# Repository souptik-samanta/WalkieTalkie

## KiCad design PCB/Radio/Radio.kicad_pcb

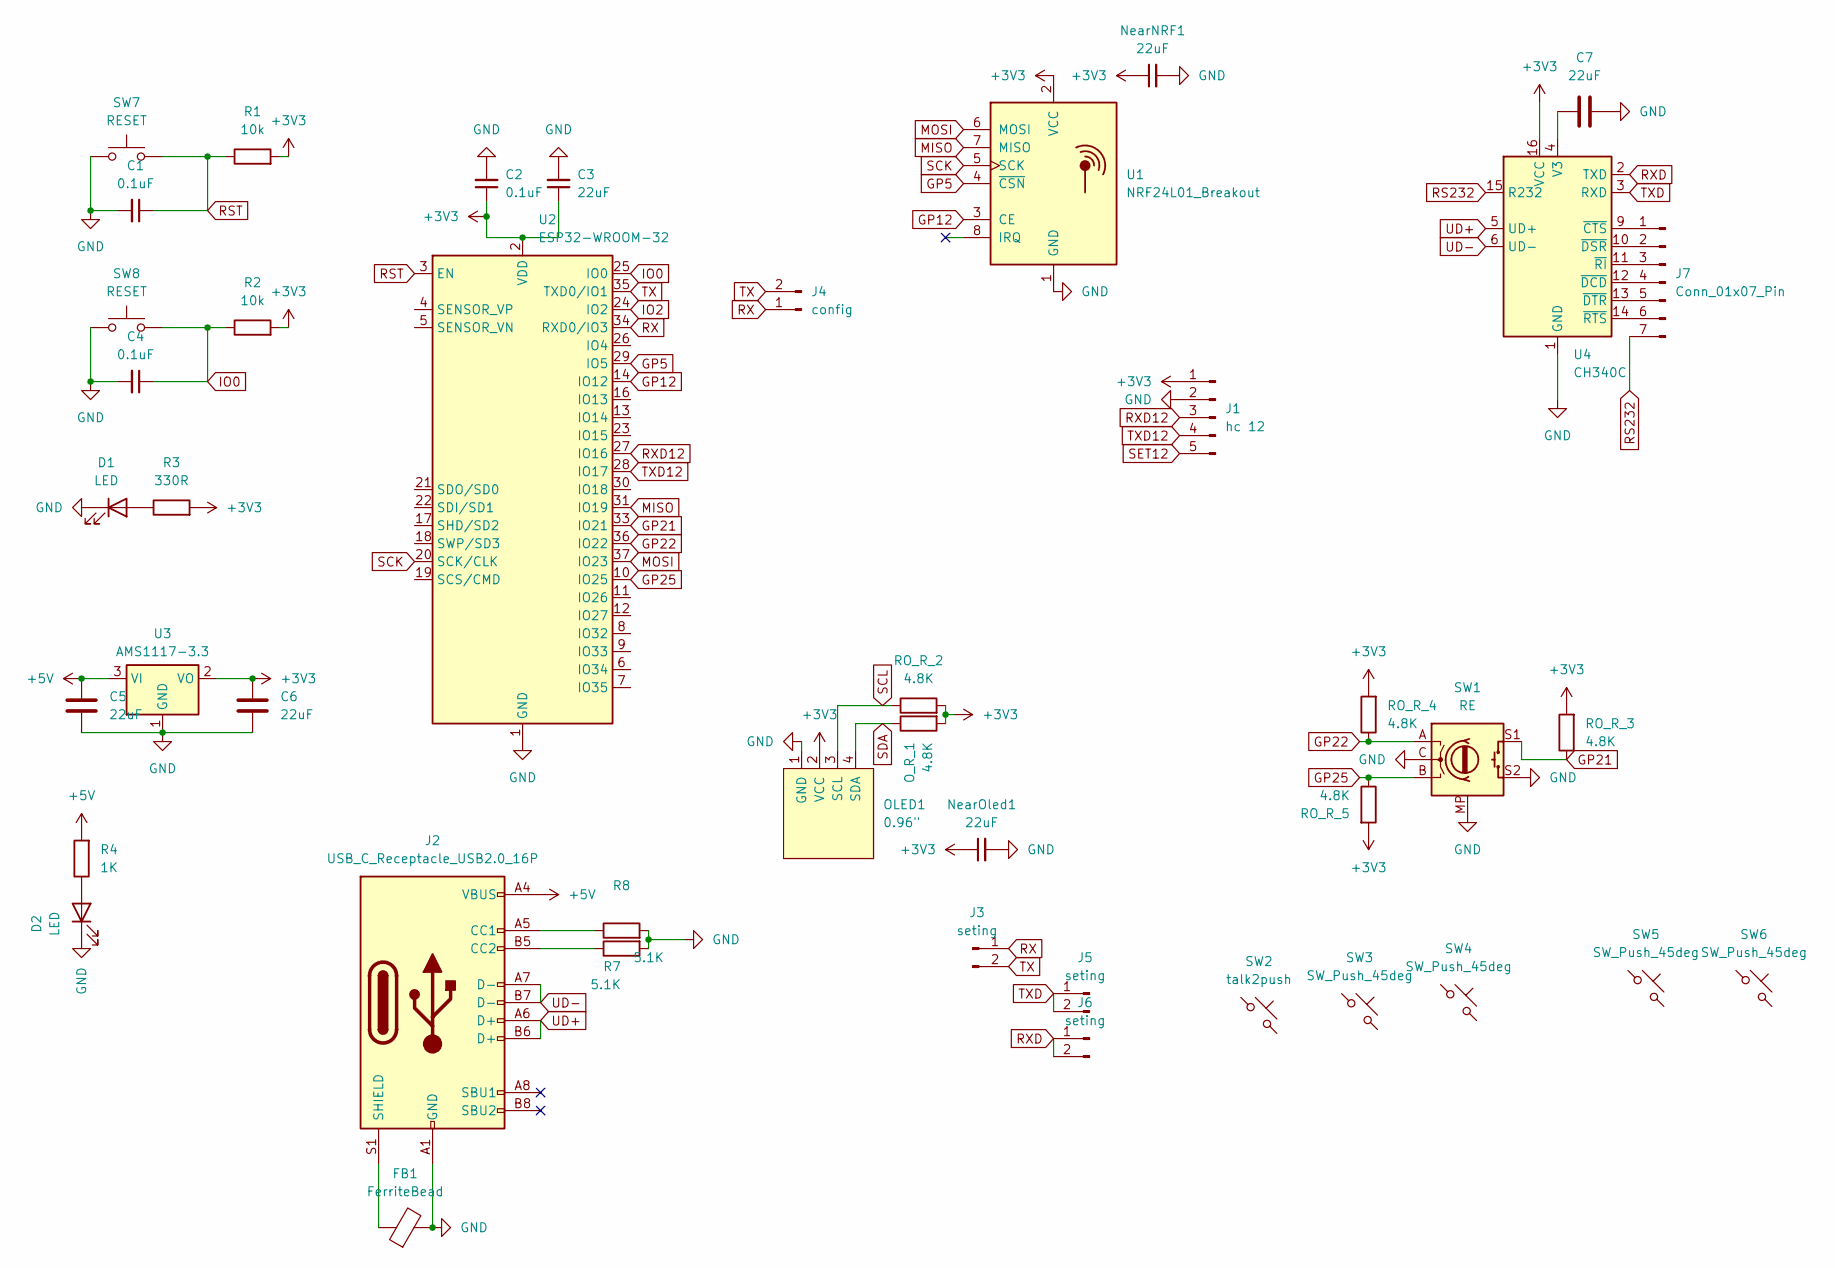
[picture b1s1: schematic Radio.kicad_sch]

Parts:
C1, C2, C4: 0.1uF; C_1206_3216Metric_Pad1.33x1.80mm_HandSolder
C3, C5, C6, C7: 22uF; C_1206_3216Metric_Pad1.33x1.80mm_HandSolder
D1, D2: LED; LED_1206_3216Metric_Pad1.42x1.75mm_HandSolder
FB1: FerriteBead; L_1206_3216Metric_Pad1.42x1.75mm_HandSolder
J1: hc 12; Hirose_DF13-05P-1.25DSA_1x05_P1.25mm_Vertical
J2: USB_C_Receptacle_USB2.0_16P; USB_C_Receptacle_HRO_TYPE-C-31-M-12
J3, J5, J6: seting; PinHeader_1x02_P2.54mm_Vertical
J4: config; PinHeader_1x02_P2.54mm_Vertical
J7: Conn_01x07_Pin; PinHeader_1x07_P2.54mm_Vertical
NearNRF1: 22uF; C_1206_3216Metric_Pad1.33x1.80mm_HandSolder
NearOled1: 22uF; C_1206_3216Metric_Pad1.33x1.80mm_HandSolder
OLED1: 0.96"; 128x64OLED
O_R_1: 4.8K; R_Axial_DIN0204_L3.6mm_D1.6mm_P7.62mm_Horizontal
R1, R2: 10k; R_Axial_DIN0204_L3.6mm_D1.6mm_P7.62mm_Horizontal
R3: 330R; R_Axial_DIN0204_L3.6mm_D1.6mm_P7.62mm_Horizontal
R4: 1K; R_Axial_DIN0204_L3.6mm_D1.6mm_P7.62mm_Horizontal
R7, R8: 5.1K; R_Axial_DIN0204_L3.6mm_D1.6mm_P7.62mm_Horizontal
RO_R_2, RO_R_3, RO_R_4, RO_R_5: 4.8K; R_Axial_DIN0204_L3.6mm_D1.6mm_P7.62mm_Horizontal
SW1: RE; RotaryEncoder_Alps_EC11E-Switch_Vertical_H20mm_MountingHoles
SW2: talk2push; SW_PUSH_6mm
SW3, SW4, SW5, SW6: SW_Push_45deg; SW_PUSH_6mm
SW7, SW8: RESET; SW_PUSH_6mm
U1: NRF24L01_Breakout; nRF24L01_Breakout
U2: ESP32-WROOM-32
U3: AMS1117-3.3; SOT-223-3_TabPin2
U4: CH340C; SOIC-16_3.9x9.9mm_P1.27mm

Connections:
+3V3: C2.1, C3.1, C6.1, J1.1, NearNRF1.1, NearOled1.1, OLED1.2 (VCC), O_R_1.2, R1.2, R2.2, R3.2, RO_R_2.2, RO_R_3.2, RO_R_4.2, RO_R_5.2, U1.2 (VCC), U2.2 (VDD), U3.2 (VO), U4.16 (VCC)
+5V: C5.1, J2.A4 (VBUS), J2.A9 (VBUS), J2.B4 (VBUS), J2.B9 (VBUS), R4.2, U3.3 (VI)
GND: C1.2, C2.2, C3.2, C4.2, C5.2, C6.2, C7.1, D1.1 (K), D2.1 (K), FB1.2, J1.2, J2.A1 (GND), J2.A12 (GND), J2.B1 (GND), J2.B12 (GND), NearNRF1.2, NearOled1.2, OLED1.1 (GND), R7.2, R8.2, SW1.C, SW1.MP, SW1.S2, SW7.1, SW8.1, U1.1 (GND), U2.1 (GND), U2.15 (GND), U2.38 (GND), U2.39 (GND), U3.1 (GND), U4.1 (GND)
GP5: U1.4 (~CSN), U2.29 (IO5)
GP12: U1.3 (CE), U2.14 (IO12)
GP21: RO_R_3.1, SW1.S1, U2.33 (IO21)
GP22: RO_R_4.1, SW1.A, U2.36 (IO22)
GP25: RO_R_5.1, SW1.B, U2.10 (IO25)
IO0: C4.1, R2.1, SW8.2, U2.25 (IO0)
IO2: U2.24 (IO2)
MISO: U1.7 (MISO), U2.31 (IO19)
MOSI: U1.6 (MOSI), U2.37 (IO23)
unnamed: D1.2 (A), R3.1
unnamed: D2.2 (A), R4.1
unnamed: J2.A5 (CC1), R8.1
unnamed: J2.B5 (CC2), R7.1
unnamed: FB1.1, J2.S1 (SHIELD)
unnamed: J7.1, U4.9 (~CTS)
unnamed: J7.2, U4.10 (~DSR)
unnamed: J7.3, U4.11 (~RI)
unnamed: J7.4, U4.12 (~DCD)
unnamed: J7.5, U4.13 (~DTR)
unnamed: J7.6, U4.14 (~RTS)
unnamed: C7.2, U4.4 (V3)
RS232: J7.7, U4.15 (R232)
RST: C1.1, R1.1, SW7.2, U2.3 (EN)
RX: J3.1, J4.1, U2.34 (RXD0/IO3)
RXD: J6.1, J6.2, U4.2 (TXD)
RXD12: J1.3, U2.27 (IO16)
SCK: U1.5 (SCK), U2.20 (SCK/CLK)
SCL: OLED1.3 (SCL), RO_R_2.1
SDA: OLED1.4 (SDA), O_R_1.1
SET12: J1.5
TX: J3.2, J4.2, U2.35 (TXD0/IO1)
TXD: J5.1, J5.2, U4.3 (RXD)
TXD12: J1.4, U2.28 (IO17)
UD+: J2.A6 (D+), J2.B6 (D+), U4.5 (UD+)
UD-: J2.A7 (D-), J2.B7 (D-), U4.6 (UD-)

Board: 2 copper layers, 43 parts (0 on the bottom side), 36 nets, no tracks yet.

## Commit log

2025-05-25 first
2025-06-08 todays log
